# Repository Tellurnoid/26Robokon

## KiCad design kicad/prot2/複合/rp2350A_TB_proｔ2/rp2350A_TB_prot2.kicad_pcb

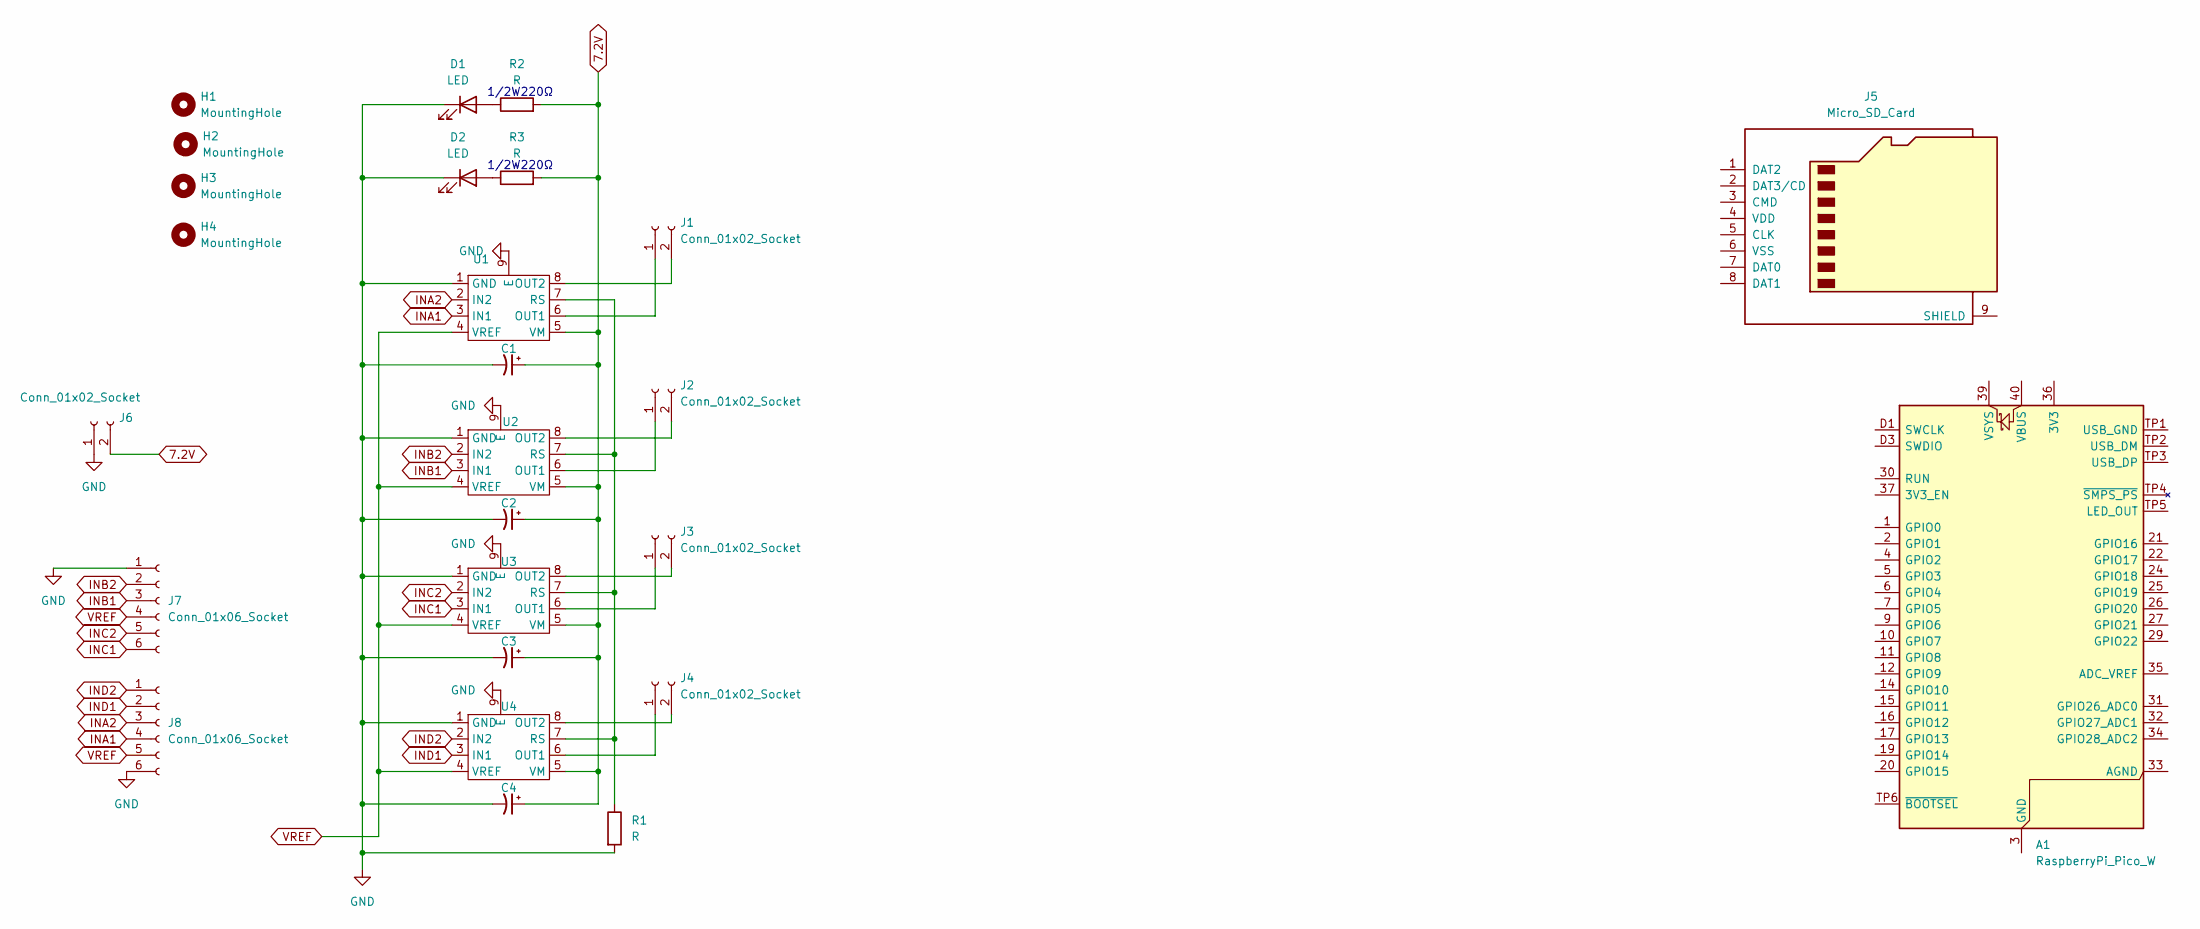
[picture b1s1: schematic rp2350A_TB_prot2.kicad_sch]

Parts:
A1: RaspberryPi_Pico_W; RaspberryPi_Pico_W_SMD
C1, C2, C3, C4: C_Polarized_Small_US; CP_Radial_D6.3mm_P2.50mm
D1, D2: LED; LED_0603_1608Metric_Pad1.05x0.95mm_HandSolder
H1, H2, H3, H4: MountingHole; MountingHole_3.2mm_M3
J1, J2, J3, J4: Conn_01x02_Socket; JST_VH_B2PS-VH_1x02_P3.96mm_Horizontal
J5: Micro_SD_Card
J6: Conn_01x02_Socket; AMASS_XT60-F_1x02_P7.20mm_Vertical
J7, J8: Conn_01x06_Socket; JST_XH_S6B-XH-A_1x06_P2.50mm_Horizontal
R1, R2, R3: R; R_Axial_DIN0309_L9.0mm_D3.2mm_P12.70mm_Horizontal
U1, U2, U3, U4: HSOP-8-1EP_3.9x4.9mm_P1.27mm_EP2.3x2.3mm

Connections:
GND: C1.2, C2.2, C3.2, C4.2, D1.1 (K), D2.1 (K), J6.1, J7.1, J8.6, R1.2, U1.1 (GND), U1.9 (E), U2.1 (GND), U2.9 (E), U3.1 (GND), U3.9 (E), U4.1 (GND), U4.9 (E)
INA1: J8.4, U1.3 (IN1)
INA2: J8.3, U1.2 (IN2)
INB1: J7.3, U2.3 (IN1)
INB2: J7.2, U2.2 (IN2)
INC1: J7.6, U3.3 (IN1)
INC2: J7.5, U3.2 (IN2)
IND1: J8.2, U4.3 (IN1)
IND2: J8.1, U4.2 (IN2)
unnamed: A1.3 (GND), A1.8 (GND), A1.13 (GND), A1.18 (GND), A1.23 (GND), A1.28 (GND), A1.38 (GND), A1.D2 (GND)
unnamed: D1.2 (A), R2.1
unnamed: D2.2 (A), R3.1
unnamed: J1.1, U1.6 (OUT1)
unnamed: J1.2, U1.8 (OUT2)
unnamed: J2.1, U2.6 (OUT1)
unnamed: J2.2, U2.8 (OUT2)
unnamed: J3.1, U3.6 (OUT1)
unnamed: J3.2, U3.8 (OUT2)
unnamed: J4.1, U4.6 (OUT1)
unnamed: J4.2, U4.8 (OUT2)
unnamed: R1.1, U1.7 (RS), U2.7 (RS), U3.7 (RS), U4.7 (RS)
VCC: C1.1, C2.1, C3.1, C4.1, J6.2, R2.2, R3.2, U1.5 (VM), U2.5 (VM), U3.5 (VM), U4.5 (VM)
VREF: J7.4, J8.5, U1.4 (VREF), U2.4 (VREF), U3.4 (VREF), U4.4 (VREF)

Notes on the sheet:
1/2W220Ω

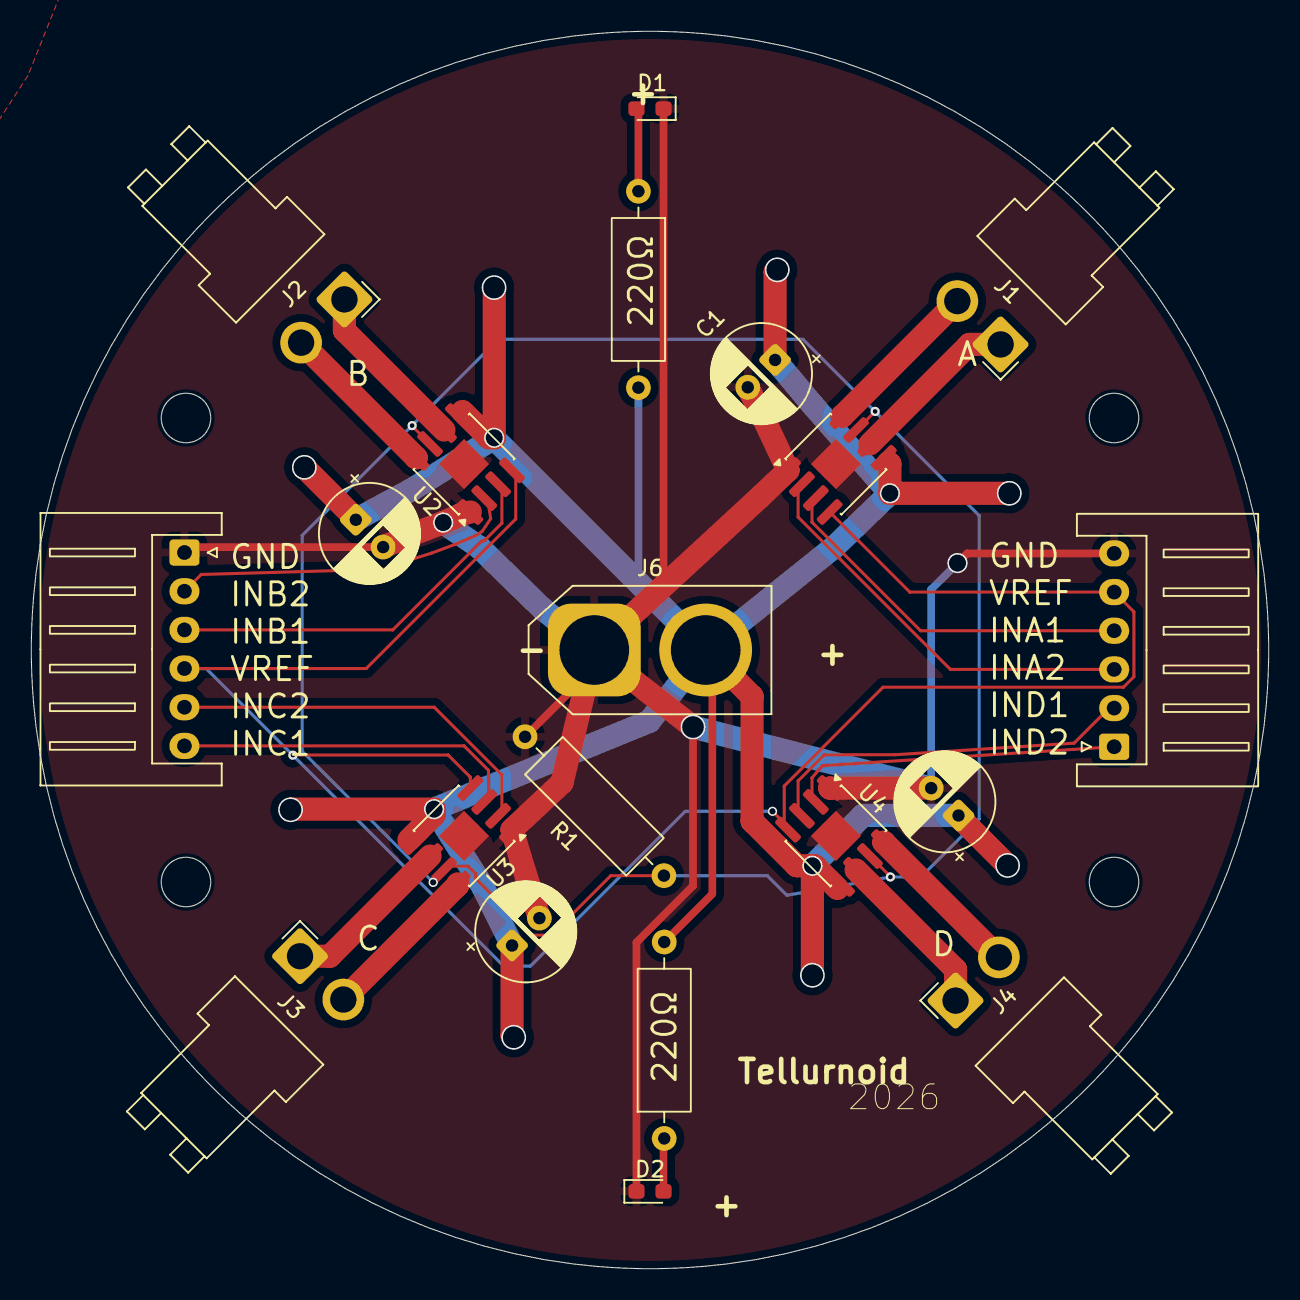
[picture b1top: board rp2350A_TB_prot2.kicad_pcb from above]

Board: 2 copper layers, 80.0 x 80.0 mm, 24 parts (0 on the bottom side), 22 nets.

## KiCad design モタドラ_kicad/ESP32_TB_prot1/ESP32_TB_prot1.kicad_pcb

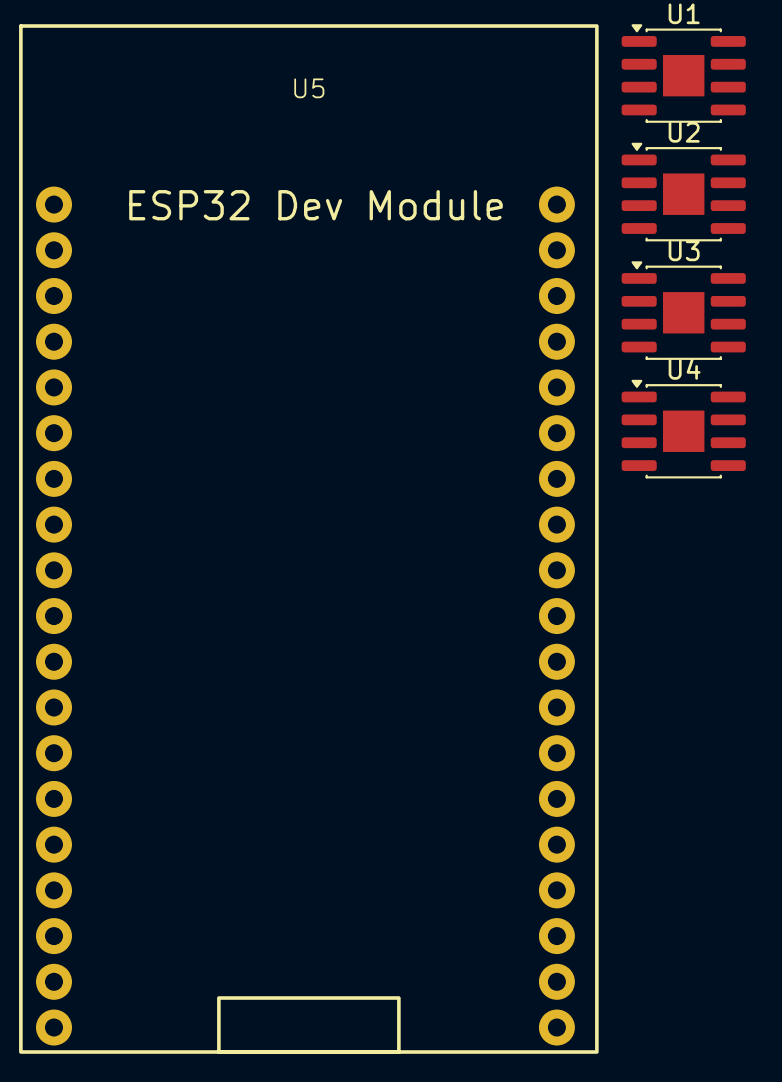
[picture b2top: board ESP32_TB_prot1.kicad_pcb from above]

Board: 2 copper layers, 5 parts (0 on the bottom side), 12 nets, no tracks yet.

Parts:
U1, U2, U3, U4: HSOP-8-1EP_3.9x4.9mm_P1.27mm_EP2.3x2.3mm
U5: ESP32_devModule

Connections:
GND: U1.1 (GND), U2.1 (GND), U3.1 (GND), U4.1 (GND)
INA1: U1.3 (IN1), U5.31 (19,MISO)
INA2: U1.2 (IN2), U5.30 (18,SCK)
INB1: U2.3 (IN1), U5.8 (33)
INB2: U2.2 (IN2), U5.7 (32)
INC1: U3.3 (IN1), U5.10 (26,DAC_2)
INC2: U3.2 (IN2), U5.9 (25,DAC_1)
IND1: U4.3 (IN1), U5.15 (13)
IND2: U4.2 (IN2), U5.11 (27)
unnamed: U1.7 (RS), U2.7 (RS), U3.7 (RS), U4.7 (RS)
unnamed: U1.5 (VM), U2.5 (VM), U3.5 (VM), U4.5 (VM)
unnamed: U1.4 (VREF), U2.4 (VREF), U3.4 (VREF), U4.4 (VREF)

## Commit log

2026-01-18 モラドラ完成
2026-01-19 消費電流メモ追加
2026-01-20 こんとろーらー開始
2026-01-24 起動音少し
